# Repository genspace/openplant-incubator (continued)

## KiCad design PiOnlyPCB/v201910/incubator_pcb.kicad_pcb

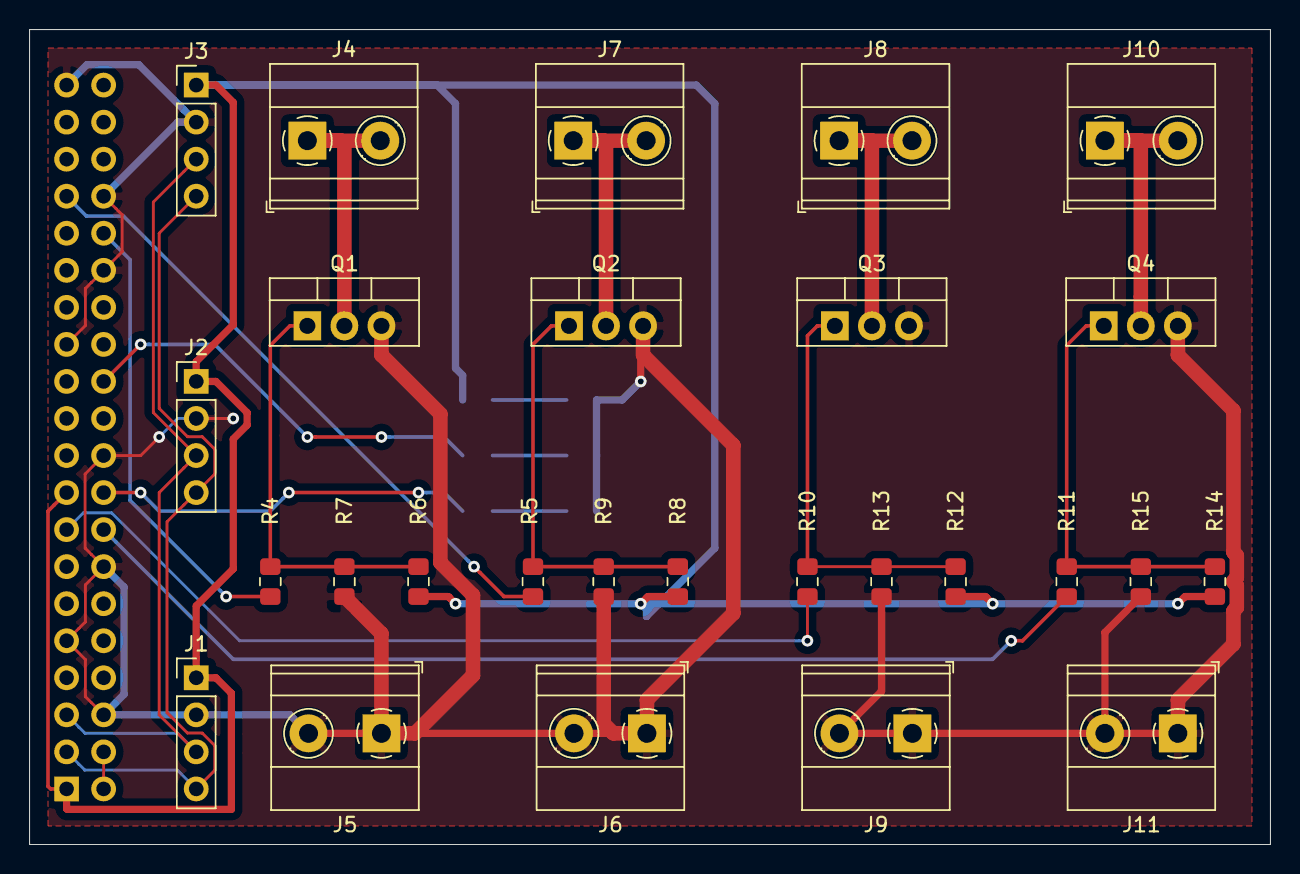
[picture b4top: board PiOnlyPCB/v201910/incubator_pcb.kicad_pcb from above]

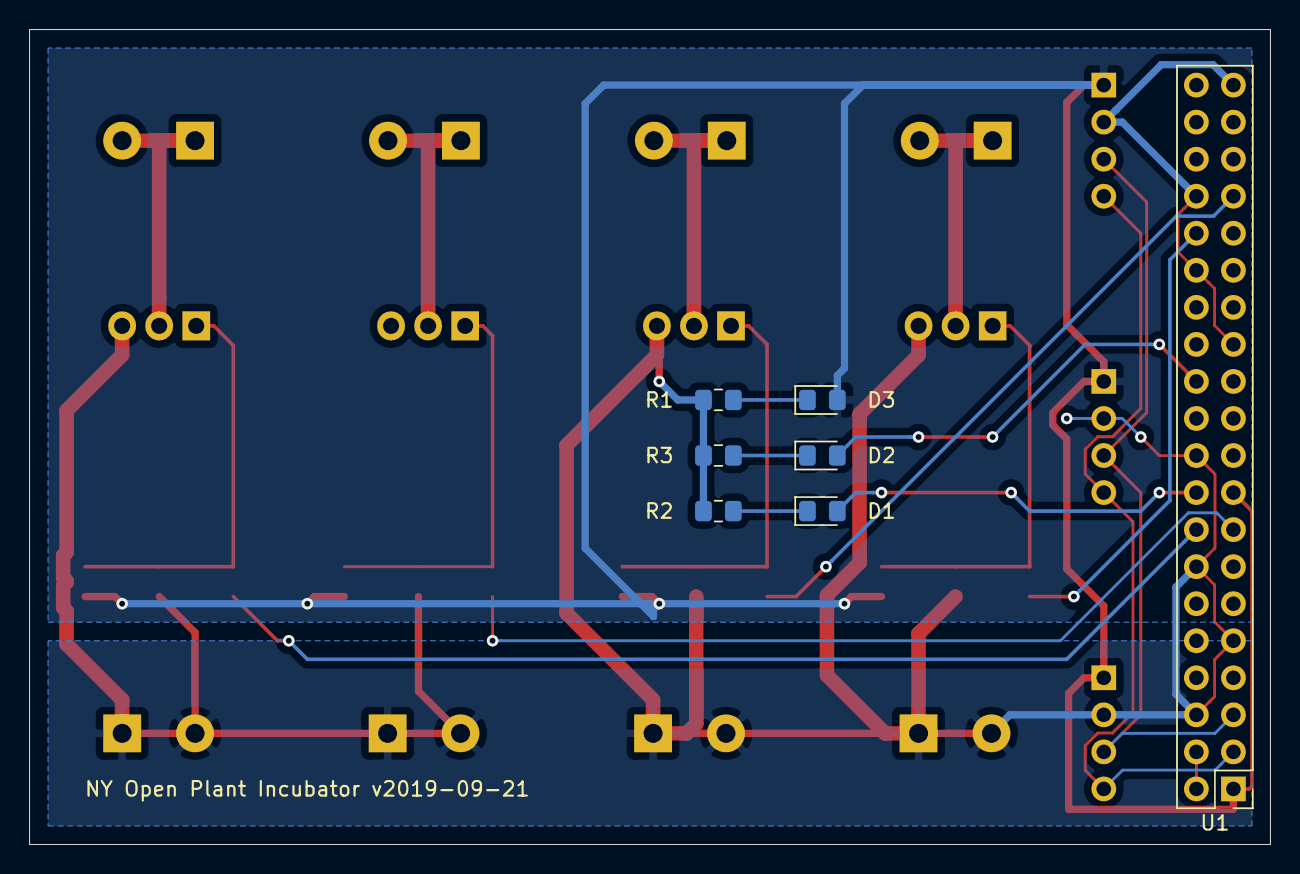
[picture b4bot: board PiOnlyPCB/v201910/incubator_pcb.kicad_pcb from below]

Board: 2 copper layers, 85.1 x 55.9 mm, 34 parts (7 on the bottom side), 22 nets.

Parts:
D1, D2, D3: LED; D_0805_2012Metric_Pad1.15x1.40mm_HandSolder
J1, J2, J3: Conn_01x04; PinHeader_1x04_P2.54mm_Vertical
J4, J5, J6, J7, J8, J9, J10, J11: Conn_01x02; TerminalBlock_Phoenix_MKDS-1,5-2_1x02_P5.00mm_Horizontal
Q1, Q2, Q3, Q4: Q_NMOS_GDS; TO-220-3_Vertical
R1, R2, R3, R4, R5, R6, R7, R8, R9, R10, R11, R12, R13, R14, R15: R_Small; R_0805_2012Metric_Pad1.15x1.40mm_HandSolder
U1: header_pi_zero_w; PinHeader_2x20_P2.54mm_Vertical

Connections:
GND: J1.2, J2.2, J3.2, J5.1, J5.2, J6.1, J6.2, J9.1, J9.2, J11.1, J11.2, Q1.3, Q2.3, Q3.3, Q4.3, R1.1, R2.1, R3.1, R7.2, R9.2, R13.2, R15.2, U1.6, U1.9, U1.14, U1.20, U1.25, U1.30, U1.34, U1.39
GPIO2_I2C1_SCL: J1.3, J2.3, J3.3, U1.5
GPIO2_I2C1_SDA: J1.4, J2.4, J3.4, U1.3
GPIO12_PWM0: R4.2, U1.32
GPIO13_PWM1: R5.2, U1.33
GPIO22: R10.2, U1.15
GPIO23: R11.2, U1.16
unnamed: D1.1, R2.2
unnamed: D1.2, U1.18
unnamed: D2.1, R3.2
unnamed: D2.2, U1.24
unnamed: D3.1, R1.2
unnamed: J4.1, J4.2, Q1.2
unnamed: J7.1, J7.2, Q2.2
unnamed: J8.1, J8.2, Q3.2
unnamed: J10.1, J10.2, Q4.2
unnamed: Q1.1, R4.1, R6.2, R7.1
unnamed: Q2.1, R5.1, R8.2, R9.1
unnamed: Q3.1, R10.1, R12.2, R13.1
unnamed: Q4.1, R11.1, R14.2, R15.1
VCC3V3: D3.2, J1.1, J2.1, J3.1, R6.1, R8.1, R12.1, R14.1, U1.1, U1.17
VCC5V: U1.2, U1.4

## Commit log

2018-05-28 update before branch for alternate component
2018-05-28 first commit getting the new clock integrated into the system. PID not working.
2018-05-28 PID operational, needs tuning
2018-05-28 fiddling with timer 2 trying to get a PWM fan control signal
2018-05-28 Initialize Express.js app
2018-05-29 Serve index.html
2018-06-04 update the filename to save logs to
2018-06-04 update fan control
2018-06-08 add more reporting paramaters and fix mapped fan duty cycle
2018-06-10 update some fan control things
2018-06-11 update the circuit diagram
2018-06-11 prepared the routing to get a better idea of how how to simplify the wiring
2018-06-15 more diagrams and changed the chipselect pin
2018-06-15 tests for the various components
2018-06-29 update tests
2018-06-30 update the PID control with bang bang and new parameters
2018-07-03 new log data to test PID and add in night cycle
2018-07-07 analysis of the few days of incubator test data
2018-07-10 in progress analysis of the incubator responding to disturbances
2018-07-10 updated analysis
2018-07-11 update the gitignore
2018-07-11 version 1 of the analysis of the incubator
2018-07-11 update the gitignore properly...
2018-07-11 resolved merge conflict by preserving the commented out pins
2018-07-11 clean up the file structre and names
2018-07-12 remove redundant data logging
2018-07-12 fix file paths, ardunio IDE needs folders
2018-07-12 update log analysis
2018-07-12 update the analysis script with comments pointing to lines to comment out because of code revision
2018-07-12 interim README update
2018-07-12 more interim updates to readme
2018-07-13 update the README to something actually readable
2018-07-13 add pull down resistors and change chip select pin
2018-08-20 playing with the tests
2018-08-20 a label for the incubators
2018-08-20 adding more logs from the first incubator created
2018-12-30 small updates before refactoring code
2019-02-11 use the local version
2019-06-29 Separating v1 and v2
2019-06-29 Pushed hardware & data analysis preliminary code
2019-06-29 Incubator is using Real Time Clock to control lights. Simplified Peltier code.
2019-06-29 Fix directory structure
2019-06-30 Added analysis code
2019-07-11 Added ipynb checkpoints to gitignore
2019-07-15 Cleaned up code for monitor
2019-07-27 Added interactivity to do thresholding
2019-07-30 added .pyc files to .gitignore
2019-07-30 added ipynb_checkpoints to gitignore
2019-07-30 added .DS_Store to gitignore
2019-07-30 added data directories to gitignore
2019-08-17 moved files into own module
2019-08-17 added __init__ to turn directory into module
2019-08-17 changed file names to remove func
2019-08-17 changed file name to processing.py
2019-08-17 Added camera code
2019-08-19 Renamed notebooks;
2019-08-28 Setup local pipeline
2019-08-30 Added s3 uploaded of processed and final image to combined script
2019-08-31 Added skeleton for database connection and upload code.
2019-08-31 Added bash script to run process_all.py and edited said python file to sync with the script
2019-10-12 update docker-compose
2019-10-12 Test program to verify the wiring is correct.
2019-10-12 Create docker file setup
2019-10-12 Complete docker-compose sqlite test
2019-10-12 Add alembic and environment variables
2019-10-12 Added band count code and put resulting barcode in file name
2019-10-21 added new line at end of file
2019-10-21 added PyMySQL to requirements.txt
2019-10-21 added MAriaDB Container for storage for app
2019-10-21 changed schema to make strings have fixed size
2019-10-21 added sleep to give database time to intialize
2019-10-21 moved data from db.env to docker-compose.yml
2019-10-21 removed blank file
2019-10-31 Add terraform script
2019-11-01 reconfigure connection string
2019-11-01 Update app setup
2019-11-02 Updated READMEs
2019-11-02 Update camera script
    Replaced placeholders with calls to env variables, and added code to delete pictures from pi
2019-11-02 Updated READMEs
    Condensed all the READMEs into one file
2019-11-03 Update Incubator Files
    Separated the incubator files by those on the arduino vs those on the pi
2019-11-04 Refactor project structure
2019-11-04 Update docker context
2019-11-04 Update dir structure
2019-11-04 Update docker-compose context
2019-11-10 Restructure directory
2019-11-10 Add util file
2019-11-10 Update credentials
2019-11-10 Update deployment params
2019-11-10 Update ssh script
2019-11-10 Add new model
2019-11-10 Place alembic at top level
2019-11-10 Add incubator.env
2019-11-10 Add sensor logging init
2019-11-10 Update start sensor logging
2019-11-10 Add logging to log sensor data
2019-11-10 Undo f string dependence
2019-11-10 Add call to update pythonpath
2019-11-10 Update sensor logging
2019-11-10 Update regex mapping
2019-11-10 Update value_dict creatiomn
2019-11-10 Add autoincrement flags
2019-11-10 Add more sensor logging
2019-11-10 Update repr
2019-11-10 Update data upload
2019-11-10 Update incubator query
2019-11-10 Update query result
2019-11-10 Add updated logic
2019-12-14 Add unique constraint to incubator number
2019-12-14 Add sleep time to log sensor
2019-12-14 Fix time delay
2020-01-06 Update sensor data script
2020-01-07 Update Dockerfile for jupyter
2020-01-07 Update instance size
2020-01-14 Add KiCad files for RaspberryPi only version 2019-10.
2020-01-26 Changing temp and adding supporting files.
2020-09-19 Added notebook which was previously its own repo
2020-09-21 Update schema models
2020-09-21 Update setup / include metabase
2020-09-21 Add schema update
2020-09-21 del db.env
2020-09-26 Cleaned up code for calculating size and health
2020-09-26 Consolidated notebook pipeline code
2020-09-27 Added test folder to gitignore
2020-10-10 Add new raspberry scripts
2020-10-14 Add db logging to basic_all script
2020-10-16 Add setup script
2020-10-16 Add setup utils
2020-10-17 Add config values
2020-10-17 Add encrypted creds
2020-10-17 Add dotenv support for secrets
2020-10-17 Push latest base config
2020-10-17 Add sensor record to log
2020-10-17 Set logging for config
2020-10-17 Update dotenv requirement
2020-10-17 Update unpacking of creds
2020-10-17 Add logging to unpack cred path
2020-10-17 Add cowsay egg
2020-10-17 Bump version
2020-10-17 Update light time store type
2020-10-17 Fix typo
2020-10-17 Update control logic
2020-10-17 Add pymysql
2020-10-17 Update logic
2020-10-17 Change id scheme
2020-10-17 Update incubator id fetch script
2020-10-17 Remove update from pip install
2020-10-17 Update query pattern
2020-10-17 Remove unused inport
2020-10-17 Add setup install
2020-10-17 Update error handling
2020-10-17 Remove lint error
2020-10-24 Push 0.44 with latest setup utils
2020-10-24 Remove post install script
2020-10-24 Bump version - add fstring
2020-10-24 Add test camera script
2020-10-24 Bump version number
2020-10-24 Change picture location
2020-11-01 Remove band wrap code for previous idea of ids for plates
2020-11-01 Finished prototyping area and health calculation in jupyter
2020-11-01 Got rid of complicated calculation code from before
2020-11-01 Completed fixing calculation of size and health
2020-11-02 Added output of photos used for area and health calculation
2020-11-03 Fix merge conflicts
2020-11-07 Revert file to working version
2020-11-07 Update basic all to work without logging sensor value to database if I2C not enabled
2020-11-11 Create new folder for setup documentation
2020-11-14 Testing a pull request.
2020-11-23 Update camera resolution config
2020-11-23 Add pool recycling
2020-11-24 Change db connect to create new session each time
2020-11-24 Update session handling
2020-12-05 Nest picture in call to is lights on
2020-12-05 Create Setup folder
    Copies files over from Eugene's Github Raspberry Pi and software setup
2021-01-18 Bump version / add new params to config
2021-01-18 Remove code to cause failure due to bad db connection
2021-01-18 Apply intervals to time deltas
2021-01-20 Change cycle time / remove heartbeat
2021-01-21 Change logging / test autocommit
2021-01-21 Change db handling
2021-01-22 Swap subtraction
2021-02-08 Copy version
2021-02-21 Partial version with GPIO expander too.
2021-02-27 PiOnlyPCB 202102: Routed again without I2C expanders, before IN* nets routed.
2021-02-27 Routed signals
2021-02-28 PCB Ready to order. Passed DRC.
2021-03-01 Update basic_all.py
    Update CAMERA_FREQ_SECONDS even if lights are off. Only take picture if lights are on.
2021-03-02 Update basic_all.py
    Update error handling to attempt on next cycle
2021-03-02 v202102 sent out to fab.
2021-03-13 Render PCB for upload.
2021-12-31 Retry changes per Jeremy and flake8 fixes.
2022-01-02 Fixing sensor bug.
2022-01-02 Added logging for time interval recording.
2022-10-29 Rename PiOnlyPCB as v3 to improve discoverability
2022-10-29 Import mainboard style v4 PCB from 2022-02-20.
2026-01-04 checking in all files for the esp32 incubator
2026-01-04 moved old designs into archive directory. renamed new control board directory
2026-01-04 readme update
